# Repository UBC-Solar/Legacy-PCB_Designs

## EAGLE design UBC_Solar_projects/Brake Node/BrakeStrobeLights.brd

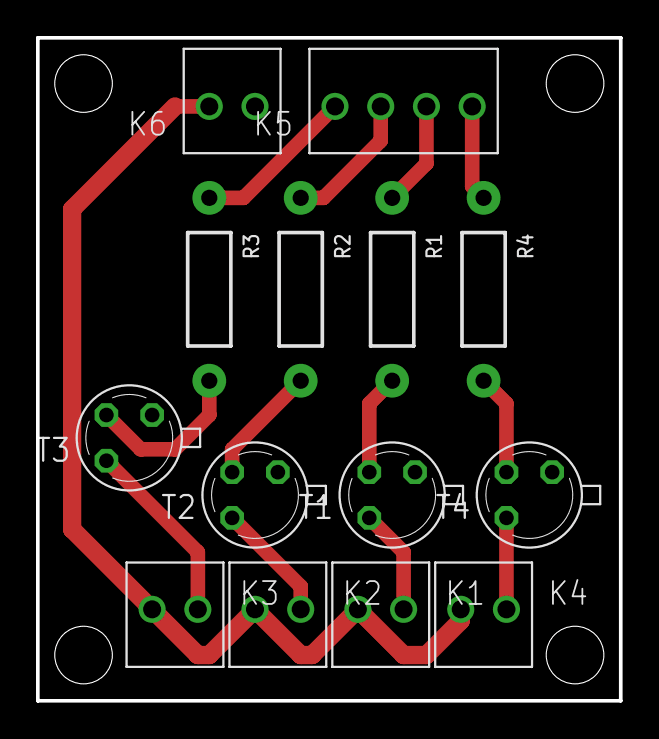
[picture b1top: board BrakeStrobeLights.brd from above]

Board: 2 copper layers, 32.4 x 36.8 mm, 14 parts (0 on the bottom side), 14 nets.

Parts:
K1, K2, K3, K4, K6: 61900211121
K5: 61900411121
R1, R2, R3, R4: AXIAL-0.4
T1, T2, T3, T4: 2N2222; TO18

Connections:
ARDUINO_C: K5.2, R2.P$1
ARDUINO_L: K5.3, R1.P$1
ARDUINO_R: K5.1, R3.P$1
ARDUINO_S: K5.4, R4.P$1
C: K2.1, T2.3
GND: K6.2, T1.1, T2.1, T3.1, T4.1
L: K1.1, T1.3
unnamed: R3.P$2, T3.2
unnamed: R2.P$2, T2.2
unnamed: R4.P$2, T4.2
unnamed: R1.P$2, T1.2
R: K3.1, T3.3
S: K4.1, T4.3
VCC: K1.2, K2.2, K3.2, K4.2, K6.1

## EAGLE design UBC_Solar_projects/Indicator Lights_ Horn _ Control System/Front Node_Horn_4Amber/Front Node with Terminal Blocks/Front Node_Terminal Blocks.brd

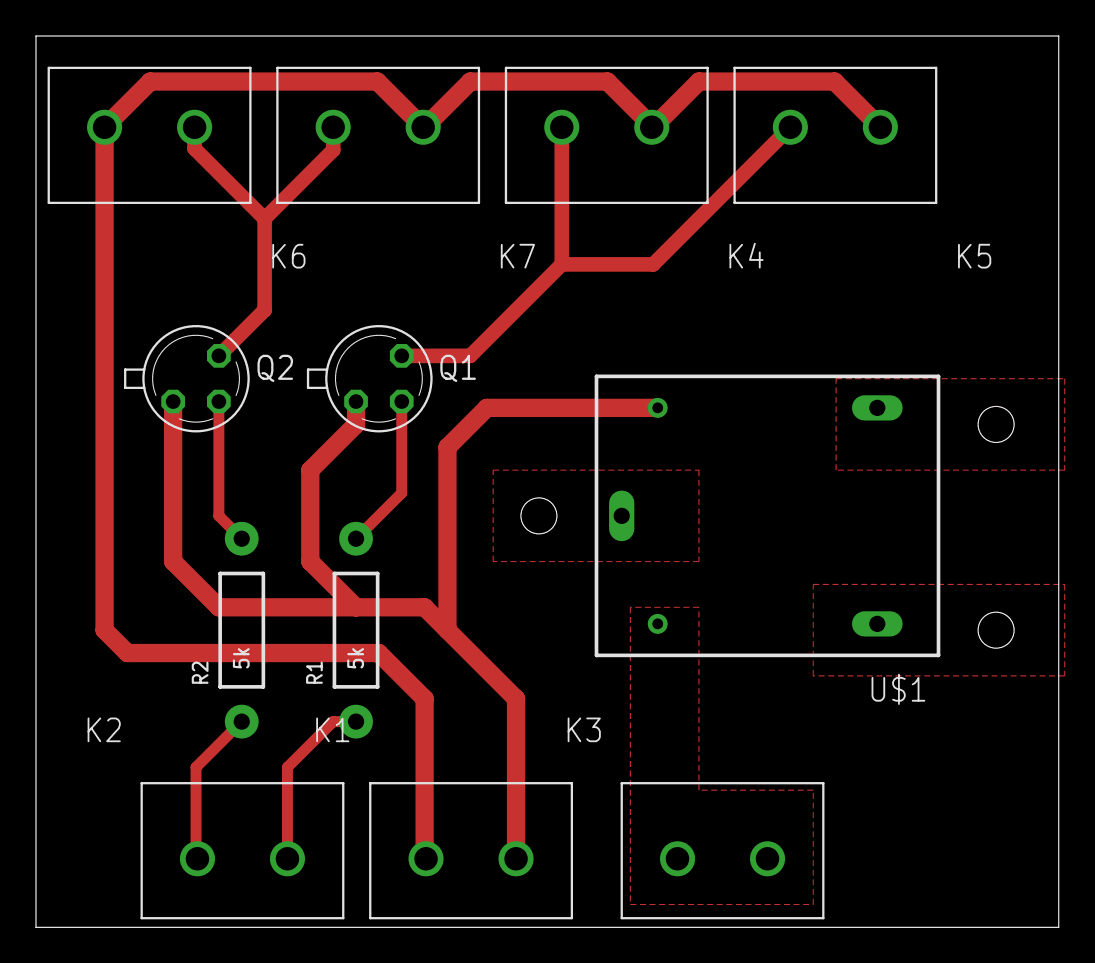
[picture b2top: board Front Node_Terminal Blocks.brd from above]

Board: 2 copper layers, 56.8 x 49.5 mm, 12 parts (0 on the bottom side), 9 nets.

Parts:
K1, K2, K3, K4, K5, K6, K7: 691102710002
Q1, Q2: 2N2222A; TO18
R1, R2: 5k; AXIAL-0.4
U$1: HRS4H-S-DC5V; RELAY

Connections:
ARDUINO_L: K2.2, R1.P$1
ARDUINO_R: K2.1, R2.P$1
GND: K1.2, Q1.1, Q2.1, U$1.COIL-2
L: K4.2, K5.2, Q1.3
unnamed: Q2.2, R2.P$2
unnamed: Q1.2, R1.P$2
R: K6.1, K7.2, Q2.3
SWITCH: K3.1, K3.2, U$1.COIL-1
VCC: K1.1, K4.1, K5.1, K6.2, K7.1

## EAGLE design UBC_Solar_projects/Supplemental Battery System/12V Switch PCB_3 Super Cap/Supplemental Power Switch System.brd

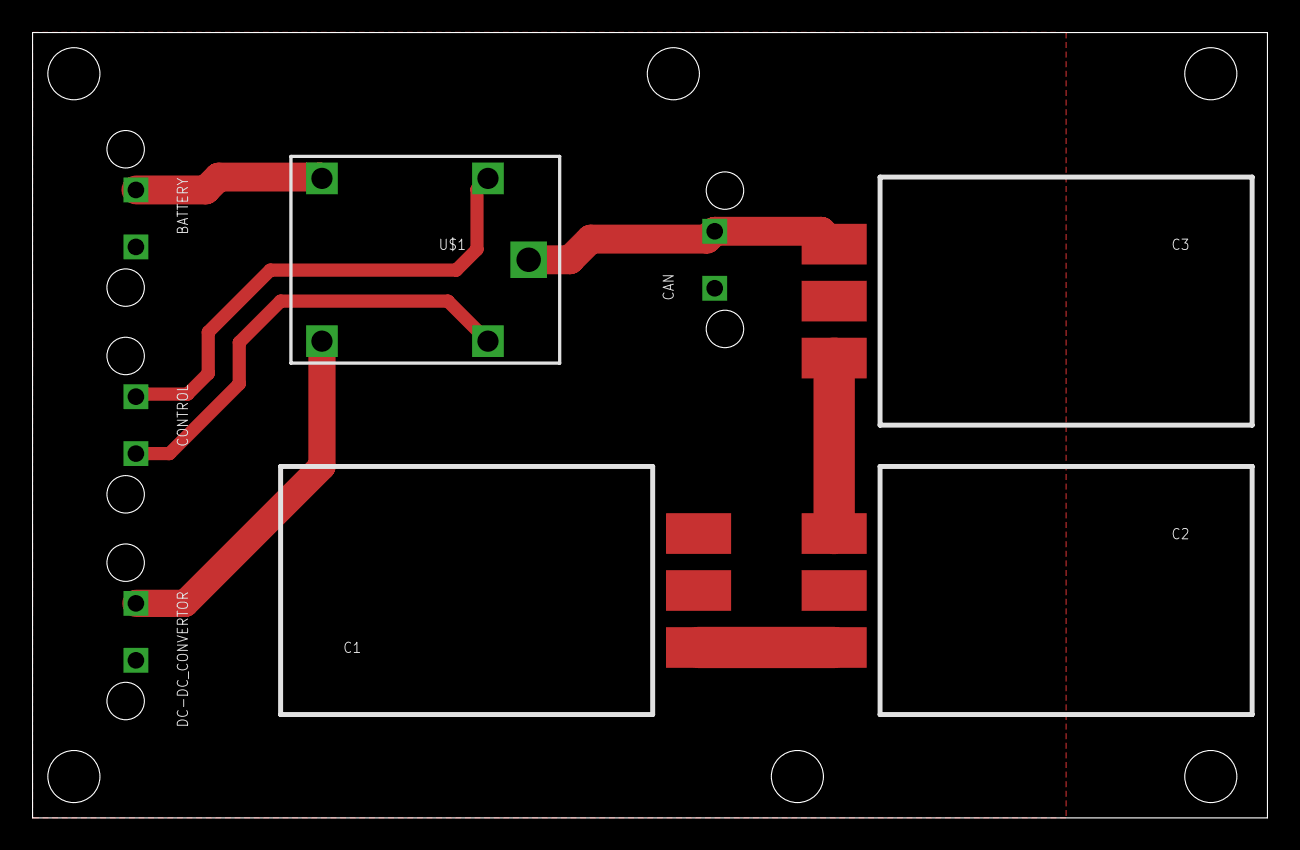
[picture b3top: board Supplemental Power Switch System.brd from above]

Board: 2 copper layers, 75.9 x 48.2 mm, 9 parts (0 on the bottom side), 8 nets.

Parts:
BATTERY: MOLEX-ULTRA-FIT; MOLEX-172287
C1, C2, C3: SUPER-CAPACITOR; DMF
CAN: MOLEX-ULTRA-FIT; MOLEX-172287
CONTROL: MOLEX-ULTRA-FIT; MOLEX-172287
DC-DC_CONVERTOR: MOLEX-ULTRA-FIT; MOLEX-172287
FRAME1: FRAME-LETTERNO_PACKAGE; DUMMY
U$1: SPDT_RELAY; G8QN-1C4

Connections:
12V: C3.+, CAN.2, U$1.1
GND: BATTERY.2, C1.-, CAN.1, DC-DC_CONVERTOR.2
unnamed: C1.+, C2.-
unnamed: C2.+, C3.-
NC: BATTERY.1, U$1.4
NO: DC-DC_CONVERTOR.1, U$1.3
ZEVA+: CONTROL.2, U$1.2
ZEVA-: CONTROL.1, U$1.5

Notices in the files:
parts and their libraries:
Wurth_Elektronik_Electromechanic_Wire_to: Copyright: Würth Elektronik
SparkFun-Passives: Licensing: Creative Commons ShareAlike 4.0 International - https://creativecommons.org/licenses/by-sa/4.0
